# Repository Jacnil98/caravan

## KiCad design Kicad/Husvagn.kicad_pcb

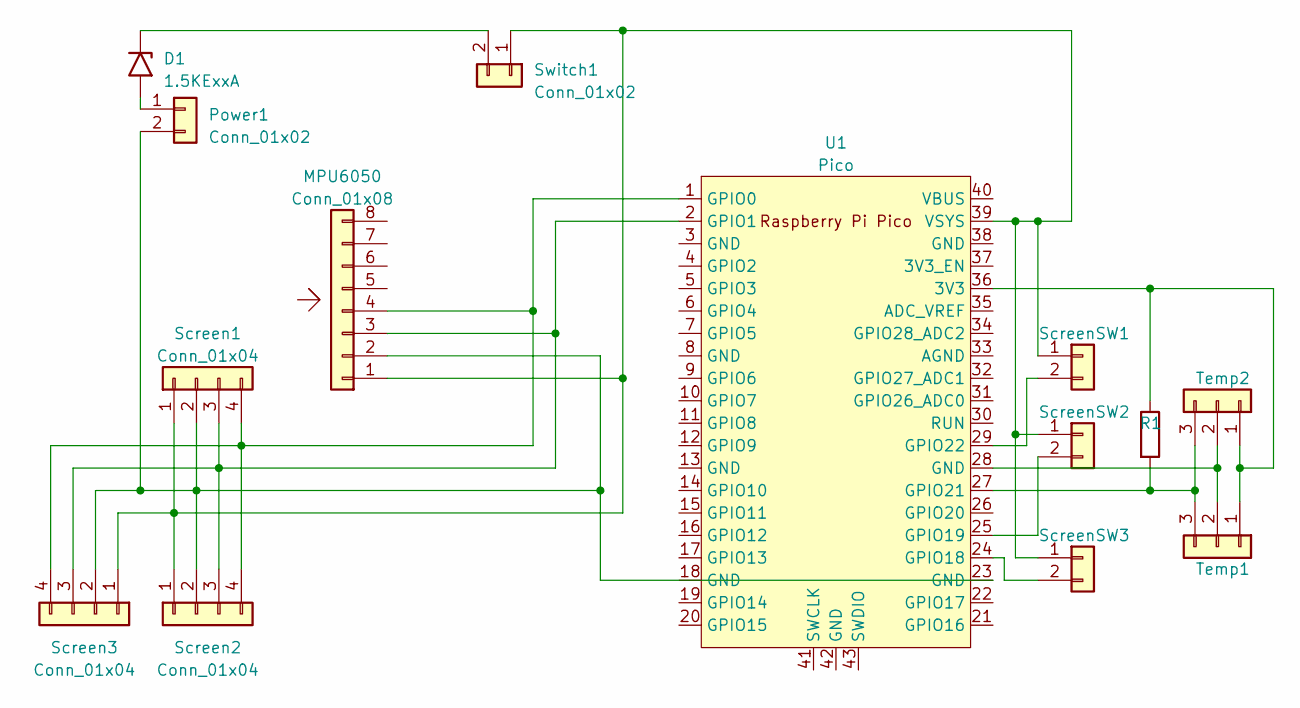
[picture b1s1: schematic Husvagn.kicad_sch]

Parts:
D1: 1.5KExxA; D_DO-201AE_P15.24mm_Horizontal
J1: Temp2; JST_XH_B3B-XH-A_1x03_P2.50mm_Vertical
J3: Temp1; JST_XH_B3B-XH-A_1x03_P2.50mm_Vertical
MPU6050: Conn_01x08; PinHeader_1x08_P2.54mm_Vertical
Power1: Conn_01x02; JST_XH_B2B-XH-A_1x02_P2.50mm_Vertical
R1: R; R_Axial_DIN0207_L6.3mm_D2.5mm_P10.16mm_Horizontal
Screen1, Screen2, Screen3: Conn_01x04; JST_XH_B4B-XH-A_1x04_P2.50mm_Vertical
ScreenSW1, ScreenSW2, ScreenSW3: Conn_01x02; JST_XH_B2B-XH-A_1x02_P2.50mm_Vertical
Switch1: Conn_01x02; JST_XH_B2B-XH-A_1x02_P2.50mm_Vertical
U1: Pico; RPi_Pico_SMD_TH

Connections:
unnamed: D1.1 (A1), Switch1.2
unnamed: D1.2 (A2), Power1.1
unnamed: J1.1, J3.1, R1.1, U1.36 (3V3)
unnamed: J1.2, J3.2, U1.28 (GND)
unnamed: J1.3, J3.3, R1.2, U1.27 (GPIO21)
unnamed: MPU6050.1, Screen1.1, Screen2.1, Screen3.1, ScreenSW1.1, ScreenSW2.1, ScreenSW3.1, Switch1.1, U1.39 (VSYS)
unnamed: MPU6050.2, Power1.2, Screen1.2, Screen2.2, Screen3.2, U1.23 (GND)
unnamed: MPU6050.3, Screen1.3, Screen2.3, Screen3.3, U1.2 (GPIO1)
unnamed: MPU6050.4, Screen1.4, Screen2.4, Screen3.4, U1.1 (GPIO0)
unnamed: ScreenSW1.2, U1.29 (GPIO22)
unnamed: ScreenSW2.2, U1.25 (GPIO19)
unnamed: ScreenSW3.2, U1.24 (GPIO18)

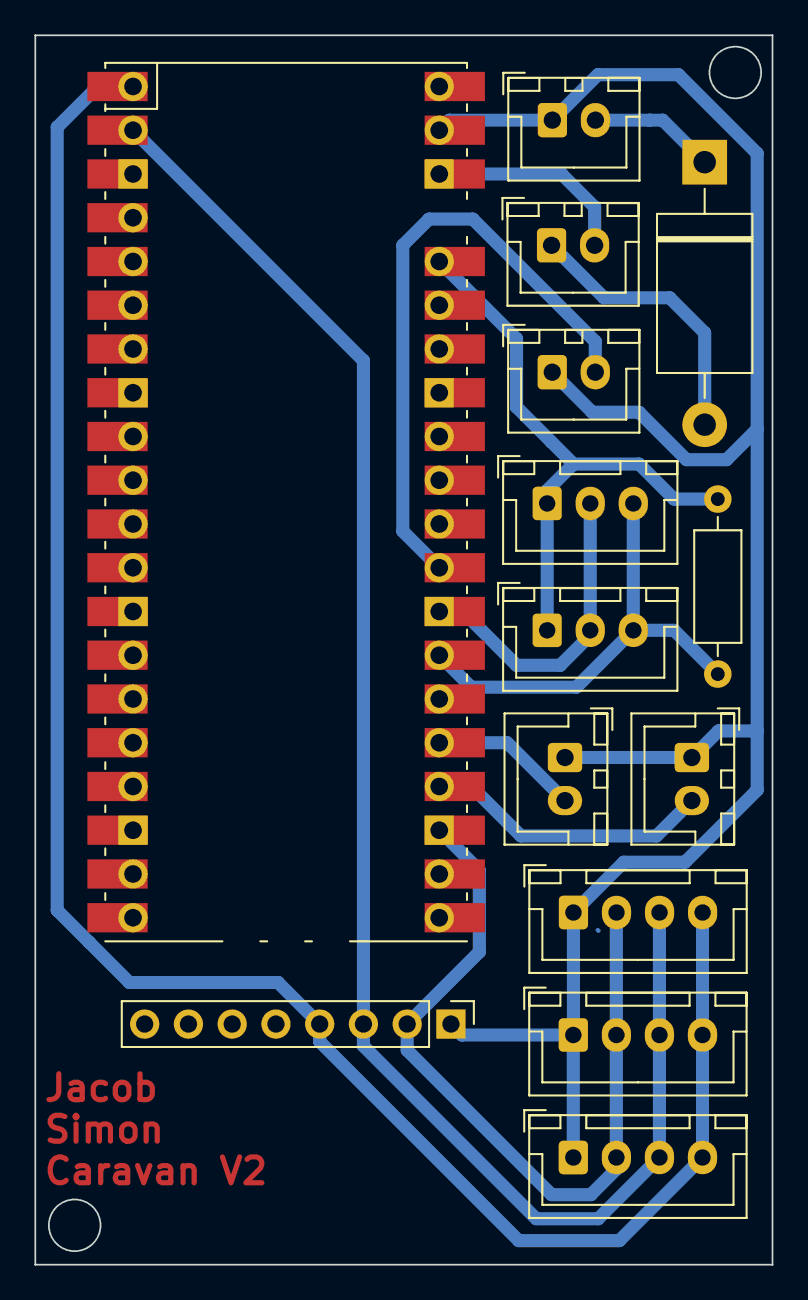
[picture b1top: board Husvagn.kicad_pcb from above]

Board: 2 copper layers, 42.8 x 71.4 mm, 14 parts (0 on the bottom side), 12 nets.

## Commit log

2023-10-04 Started test repository for OTA
2023-10-04 Added secrets and OTA working
2023-10-04 Added Lib folder
2023-10-04 Fixed the values and added CM to the tilt square
2023-10-04 Added ignore to secrets file
2023-10-08 Some design changes and added temp in html
2023-10-10 Some design changes
2023-10-10 Added another temp
2023-10-10 Added some shadow
2023-10-10 Cleaned up main file and added functions in classes
2023-10-10 Added in and out temp and possibility to add Version
2023-10-12 Added Kicad files
2023-10-12 Version, temp beside "*vagn:"
    Added version bottom off screen, version is a 1 decimal float instead of int and added the temperature value beside inom/utom vagn instead of under
